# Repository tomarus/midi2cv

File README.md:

MIARPH * MIDI2CV + ARPEGGIATOR
==============================

Miarph is an Arduino based MIDI2CV converter with 4 0-5V 12 bit DAC's and 10 trigger outputs.

## Features

* 4 individual 0-5v 12 bit DAC's (MCP4922 based)
* 10 Trigger outputs
* Dual Arpeggiator
* SYSEX configurable.
* Two MIDI-CC controller outputs.
* Two Midi Note + Trigger outputs.
* Split note (single channel) or two individual channel operations.
* 8 individually programmable gate triggers to be either drum trigger or clock divider.

## Building Notes

* Use a real Arduino Nano or atleast one with a real FTDI chip.
* There is no tuning possibility, but a stable LM7805 is key.
* The LED is on the wrong side but easy fixable using 2 short wires. (This is the only mistake on the PCB).
* The LED resistor is dependent on your LED specs.
* Capacitors have three holes, always use the square one and one of the others. Both 2.54mm and 5.08mm caps will fit.
* Polarized caps should have their positive in the square hole and the negative pointing outwards the board. (See image above!)
* Remove the jumper and power cable before programming!
* DO NOT CONNECT POWER AND USB AT THE SAME TIME!

## BUGS

* It crashes at split note change. But after a reset it is correctly read from eeprom.
* Transpose is buggy, but required because it can only support 60 MIDI notes.

## Programming Using Webconfig

See https://midi.tomarus.io/miarph/

You need a modern browser like Opera or Chrome to use this site.

Note that all values are initially *unknown* until you actually change something.
The device has no MIDI output so config values can't be read back.

After initially building the device, you should set all of your defaults once via webconfig.
After changing values it is stored on the device's eeprom and used at the next power up.

## Programming Using the Commandline

Use the ```midi2cv``` Go utility to program the device.

Example:

```./midi2cv write 0x01 0x77```

Where ```0x01``` is the address and ```0x77``` the value.

List of addresses to program:

| Address | Description | Example value |
| -- | -- | -- |
| 0x00 | unused | -- |
| 0x01 | Split keyboard at note | 0x40 (use 0x00 for no split) |
| 0x02 | MIDI 1 Channel | 0x01 |
| 0x03 | MIDI 2 Channel | 0x02 |
| 0x04 | Transpose Channel 1 | 0x40 |
| 0x05 | Transpose Channel 2 | 0x40 |
| 0x06 | Control Change Number Channel 1 | 0x07 (0x07 = volume) |
| 0x07 | Control Change Number Channel 2 | 0x6A (0x6A = filter cutoff) |
| 0x08 | Control Change Channel 1 | 0x01 |
| 0x09 | Control Change Channel 2 | 0x02 |
| 0x0a | Pitchbend Channel 1 | 0x02 (number of notes) |
| 0x0b | Pitchbend Channel 2 | 0x0c (number of notes) |
| 0x0c | Midi Channel 1 sync | 0x00 (00 = use potmeter, otherwise nr of midi clock ticks) |
| 0x0d | Midi Channel 2 sync | 0x00 (00 = use potmeter, otherwise nr of midi clock ticks) |
| 0x0e | Clockticks to advance the clock divider | 0x03 (0x03 = sync to quarter notes) |
| 0x0f | unused | -- |
| 0x10..0x18 | Port Mode (0 = clock divider, 1 = drum trigger) | 0x00 |
| 0x18..0x20 | Port Trigger Note | 0x36 |
| 0x20..0x28 | Port Clock Divider Division (0=1/1, 1=1/2, 2=1/4, 3=1/8, etc) | 0x00 |

## Bill Of Materials

|Designator                   |Package                                 |Quantity|Designation |PartNo|
|-----------------------------|----------------------------------------|--------|------------|------|
|RV1                          |Potentiometer_Alps_RK09K_Single_Vertical|1       |B10K        | |
|NANO                         |Arduino_Nano_Silk                       |1       |Nano v3     | |
|C1                           |GenericCap                              |1       |100uF       | |
|C2                           |GenericCap                              |1       |10uF        | |
|C3,C4,C5,C6,C7,C8,C9         |GenericCap                              |7       |100nF       | |
|D1                           |LED_D3.0mm                              |1       |LED         | |
|D2,D3,D4                     |D_DO-35_SOD27_P7.62mm_Horizontal        |3       |D           | |
|J1                           |PinHeader_1x02_P2.54mm_Vertical         |1       |ProgramJmpr | |
|J2                           |IDC-Header_2x05_P2.54mm_Vertical        |1       |Power       | |
|J3,J14,J15                   |PinSocket_1x04_P2.54mm_Vertical         |3       |Conn_01x04_M| |
|J4,J24,J25                   |PinHeader_1x04_P2.54mm_Vertical         |3       |Conn_01x04_F| |
|J5                           |PinSocket_1x08_P2.54mm_Vertical         |1       |Conn_01x08_M| |
|J6                           |PinHeader_1x08_P2.54mm_Vertical         |1       |Conn_01x08_F| |
|J7                           |Jack_3.5mm_QingPu_WQP-PJ366ST_Vertical  |1       |Midi Input  | |
|J8-J13,J16-J23               |Jack_3.5mm_QingPu_WQP-PJ398SM_Vertical  |14      |Misc        | |
|R1,R2                        |R_Axial_DIN0207_L6.3mm_D2.5mm_P7.62mm   |2       |2K2         | |
|R3,R4,R5,R6                  |R_Axial_DIN0207_L6.3mm_D2.5mm_P7.62mm   |4       |1K          | |
|R7                           |R_Axial_DIN0207_L6.3mm_D2.5mm_P7.62mm   |1       |220         | |
|R8,R9,R10,R11,R12,R13,R14,R15|R_Axial_DIN0207_L6.3mm_D2.5mm_P7.62mm   |8       |100         | |
|U1                           |TO-220-3_Horizontal_TabDown             |1       |L7805       | |
|U2                           |DIP-8_W7.62mm                           |1       |24LC256     | |
|U5                           |DIP-4_W7.62mm                           |1       |PC817       | PC817XNNSZ1B |
|U6,U8                        |DIP-14_W7.62mm                          |2       |TL074       | |
|U7                           |DIP-16_W7.62mm                          |1       |74HC595     | |
|U3,U4                        |DIP-14_W7.62mm                          |2       |MCP4922     | |

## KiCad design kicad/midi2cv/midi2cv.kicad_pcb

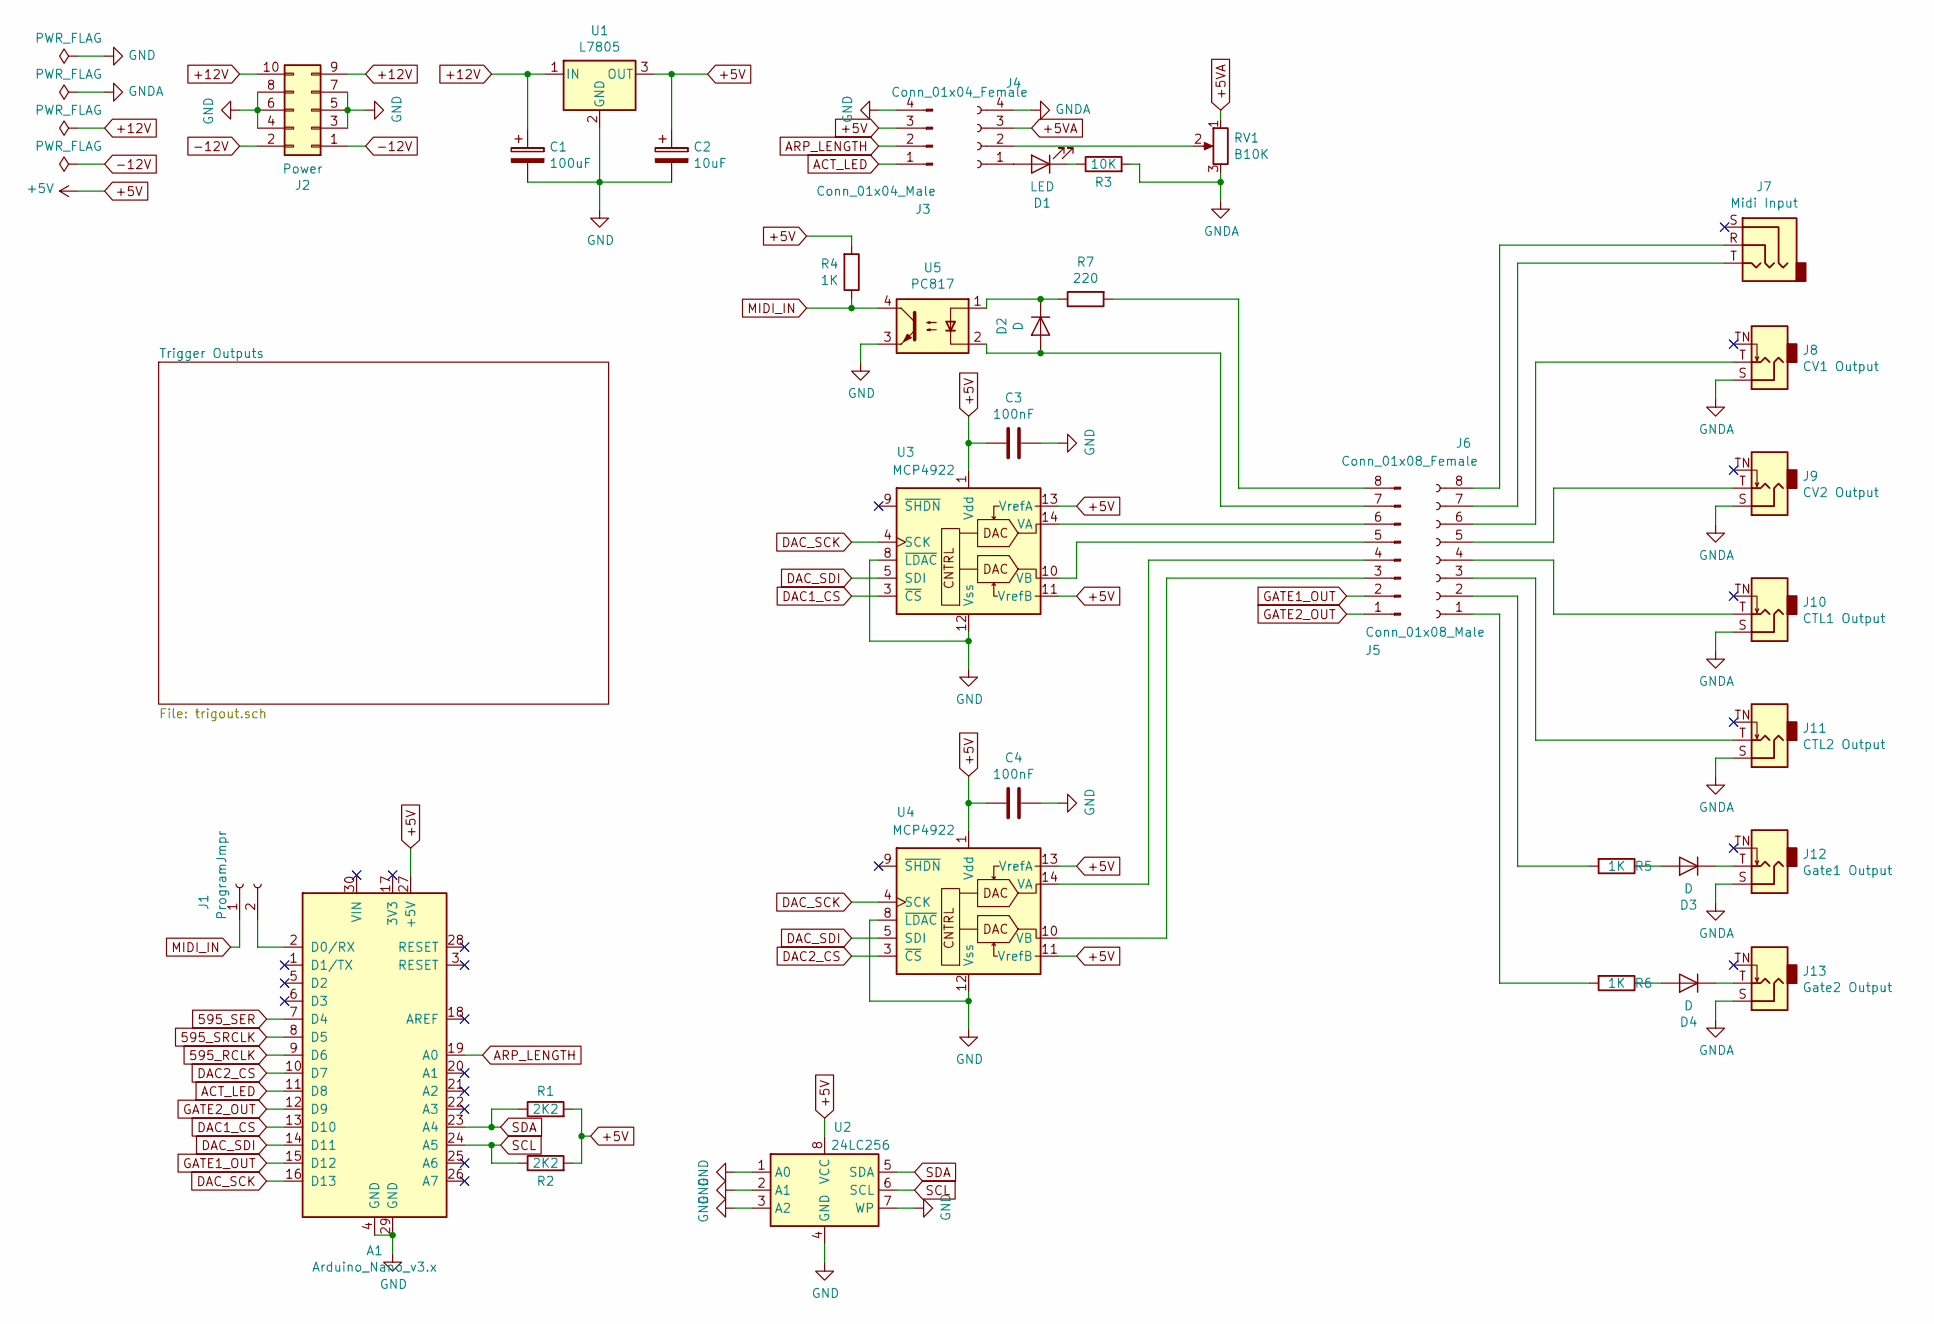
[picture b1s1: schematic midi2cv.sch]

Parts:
A1: Arduino_Nano_v3.x; Arduino_Nano_Silk
C1: 100uF; GenericCap
C2: 10uF; GenericCap
C3, C4: 100nF; GenericCap
D1: LED; LED_D3.0mm
D2, D3, D4: D; D_DO-35_SOD27_P7.62mm_Horizontal
J1: ProgramJmpr; PinHeader_1x02_P2.54mm_Vertical
J2: Power; IDC-Header_2x05_P2.54mm_Vertical
J3: Conn_01x04_Male; PinSocket_1x04_P2.54mm_Vertical
J4: Conn_01x04_Female; PinHeader_1x04_P2.54mm_Vertical
J5: Conn_01x08_Male; PinSocket_1x08_P2.54mm_Vertical
J6: Conn_01x08_Female; PinHeader_1x08_P2.54mm_Vertical
J7: Midi Input; Jack_3.5mm_QingPu_WQP-PJ366ST_Vertical_CircularHoles
J8: CV1 Output; Jack_3.5mm_QingPu_WQP-PJ398SM_Vertical_CircularHoles
J9: CV2 Output; Jack_3.5mm_QingPu_WQP-PJ398SM_Vertical_CircularHoles
J10: CTL1 Output; Jack_3.5mm_QingPu_WQP-PJ398SM_Vertical_CircularHoles
J11: CTL2 Output; Jack_3.5mm_QingPu_WQP-PJ398SM_Vertical_CircularHoles
J12: Gate1 Output; Jack_3.5mm_QingPu_WQP-PJ398SM_Vertical_CircularHoles
J13: Gate2 Output; Jack_3.5mm_QingPu_WQP-PJ398SM_Vertical_CircularHoles
R1, R2: 2K2; R_Axial_DIN0207_L6.3mm_D2.5mm_P7.62mm_Horizontal
R3: 10K; R_Axial_DIN0207_L6.3mm_D2.5mm_P7.62mm_Horizontal
R4, R5, R6: 1K; R_Axial_DIN0207_L6.3mm_D2.5mm_P7.62mm_Horizontal
R7: 220; R_Axial_DIN0207_L6.3mm_D2.5mm_P7.62mm_Horizontal
RV1: B10K; Potentiometer_Alps_RK09K_Single_Vertical
U1: L7805; TO-220-3_Horizontal_TabDown
U2: 24LC256; DIP-8_W7.62mm
U3, U4: MCP4922; DIP-14_W7.62mm
U5: PC817; DIP-4_W7.62mm

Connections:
595_RCLK: A1.9 (D6); also elsewhere on the board
595_SER: A1.7 (D4); also elsewhere on the board
595_SRCLK: A1.8 (D5); also elsewhere on the board
+5V: A1.27 (+5V), C2.1, C3.1, C4.1, J3.3, R1.2, R2.2, R4.2, U1.3 (OUT), U2.8 (VCC), U3.1 (Vdd), U3.11 (VrefB), U3.13 (VrefA), U4.1 (Vdd), U4.11 (VrefB), U4.13 (VrefA); also elsewhere on the board
+5VA: J4.3, RV1.1
+12V: C1.1, J2.9, J2.10, U1.1 (IN); also elsewhere on the board
-12V: J2.1, J2.2; also elsewhere on the board
ACT_LED: A1.11 (D8), J3.1
ARP_LENGTH: A1.19 (A0), J3.2
DAC1_CS: A1.13 (D10), U3.3 (~CS)
DAC2_CS: A1.10 (D7), U4.3 (~CS)
DAC_SCK: A1.16 (D13), U3.4 (SCK), U4.4 (SCK)
DAC_SDI: A1.14 (D11), U3.5 (SDI), U4.5 (SDI)
GATE1_OUT: A1.15 (D12), J5.2
GATE2_OUT: A1.12 (D9), J5.1
GND: A1.4 (GND), A1.29 (GND), C1.2, C2.2, C3.2, C4.2, J2.3, J2.4, J2.5, J2.6, J2.7, J2.8, J3.4, U1.2 (GND), U2.1 (A0), U2.2 (A1), U2.3 (A2), U2.4 (GND), U2.7 (WP), U3.8 (~LDAC), U3.12 (Vss), U4.8 (~LDAC), U4.12 (Vss), U5.3; also elsewhere on the board
GNDA: J4.4, J8.S, J9.S, J10.S, J11.S, J12.S, J13.S, R3.2, RV1.3; also elsewhere on the board
MIDI_IN: J1.1, R4.1, U5.4
unnamed: A1.2 (D0/RX), J1.2
unnamed: D1.1 (K), R3.1
unnamed: D1.2 (A), J4.1
unnamed: D2.1 (K), R7.1, U5.1
unnamed: D2.2 (A), J5.7, U5.2
unnamed: D3.1 (K), J12.T
unnamed: D3.2 (A), R5.1
unnamed: D4.1 (K), J13.T
unnamed: D4.2 (A), R6.1
unnamed: J4.2, RV1.2
unnamed: J5.3, U4.10 (VB)
unnamed: J5.4, U4.14 (VA)
unnamed: J5.5, U3.10 (VB)
unnamed: J5.6, U3.14 (VA)
unnamed: J5.8, R7.2
unnamed: J6.1, R6.2
unnamed: J6.2, R5.2
unnamed: J6.5, J9.T
unnamed: J6.6, J8.T
unnamed: J6.7, J7.T
unnamed: J6.8, J7.R
unnamed: J6.4, J10.T
unnamed: J6.3, J11.T
SCL: A1.24 (A5), R2.1, U2.6 (SCL)
SDA: A1.23 (A4), R1.1, U2.5 (SDA)

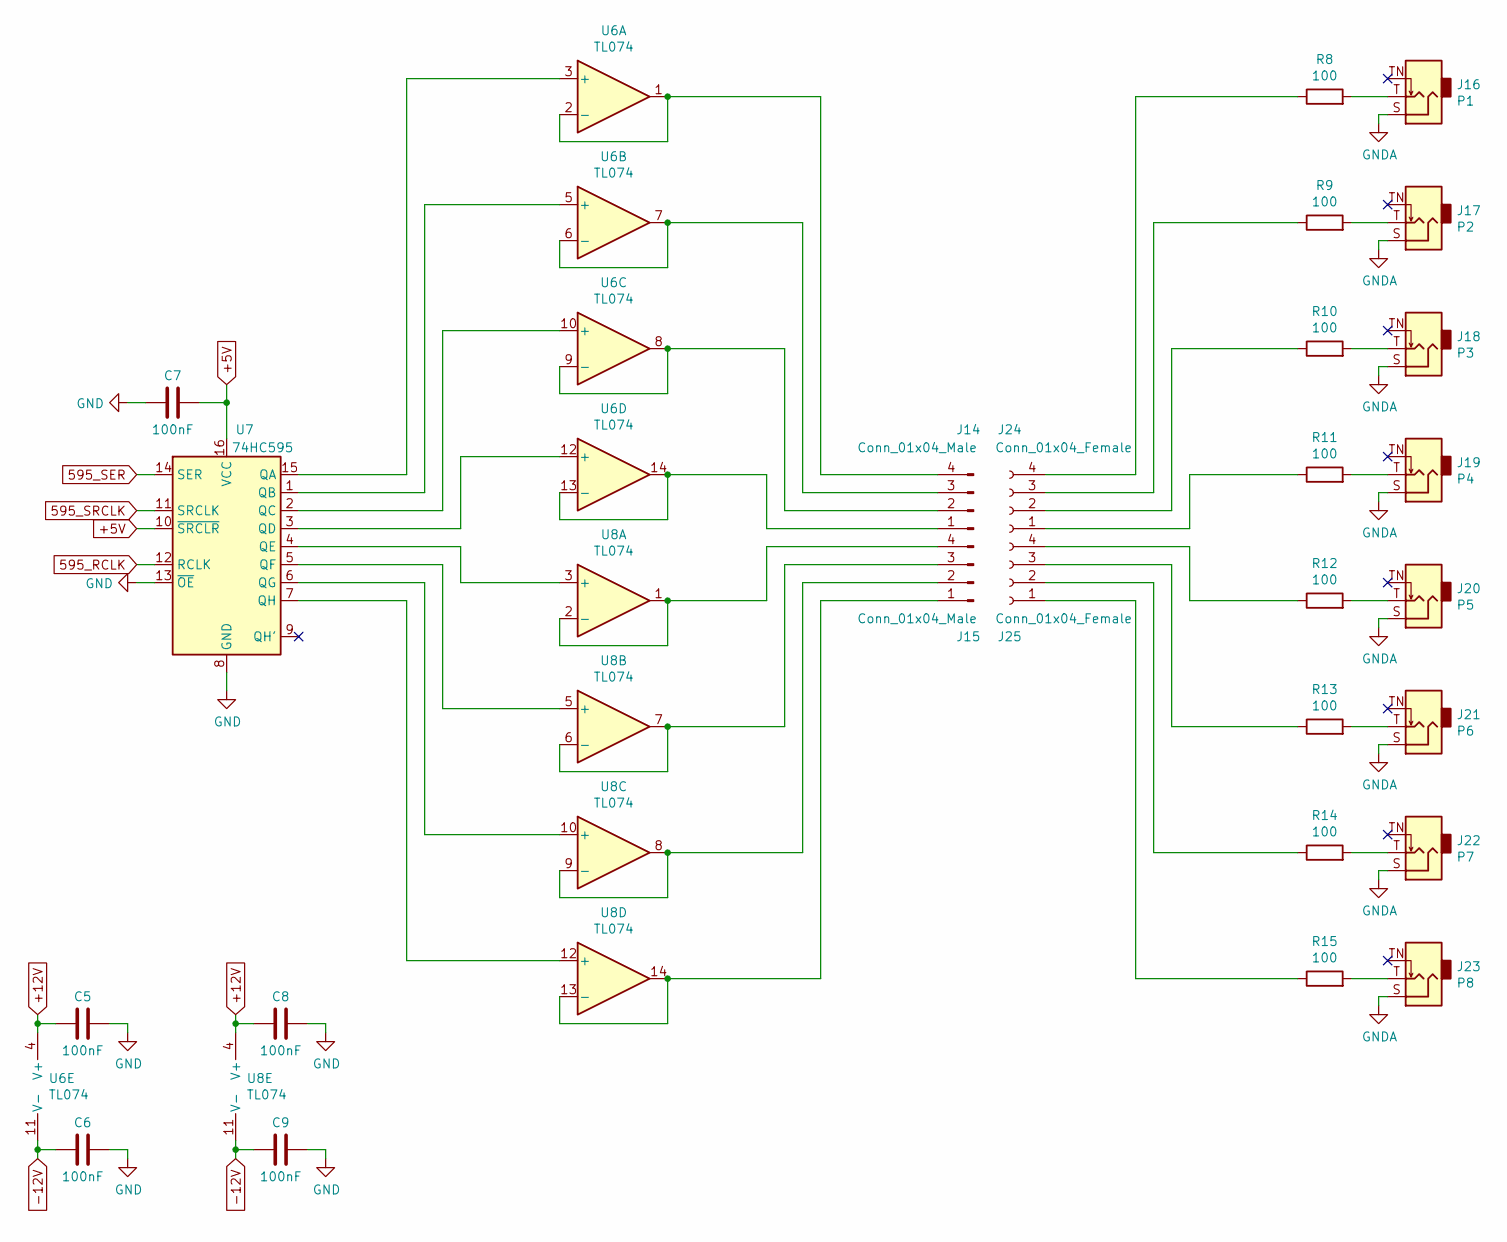
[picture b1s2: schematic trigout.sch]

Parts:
C5, C6, C7, C8, C9: 100nF; GenericCap
J14, J15: Conn_01x04_Male; PinSocket_1x04_P2.54mm_Vertical
J16: P1; Jack_3.5mm_QingPu_WQP-PJ398SM_Vertical_CircularHoles
J17: P2; Jack_3.5mm_QingPu_WQP-PJ398SM_Vertical_CircularHoles
J18: P3; Jack_3.5mm_QingPu_WQP-PJ398SM_Vertical_CircularHoles
J19: P4; Jack_3.5mm_QingPu_WQP-PJ398SM_Vertical_CircularHoles
J20: P5; Jack_3.5mm_QingPu_WQP-PJ398SM_Vertical_CircularHoles
J21: P6; Jack_3.5mm_QingPu_WQP-PJ398SM_Vertical_CircularHoles
J22: P7; Jack_3.5mm_QingPu_WQP-PJ398SM_Vertical_CircularHoles
J23: P8; Jack_3.5mm_QingPu_WQP-PJ398SM_Vertical_CircularHoles
J24, J25: Conn_01x04_Female; PinHeader_1x04_P2.54mm_Vertical
R8, R9, R10, R11, R12, R13, R14, R15: 100; R_Axial_DIN0207_L6.3mm_D2.5mm_P7.62mm_Horizontal
U6, U8: TL074; DIP-14_W7.62mm
U7: 74HC595; DIP-16_W7.62mm

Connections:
595_RCLK: U7.12 (RCLK); also elsewhere on the board
595_SER: U7.14 (SER); also elsewhere on the board
595_SRCLK: U7.11 (SRCLK); also elsewhere on the board
+5V: C7.1, U7.10 (~SRCLR), U7.16 (VCC); also elsewhere on the board
+12V: C5.2, C8.2, U6.4 (V+), U8.4 (V+); also elsewhere on the board
-12V: C6.2, C9.2, U6.11 (V-), U8.11 (V-); also elsewhere on the board
GND: C5.1, C6.1, C7.2, C8.1, C9.1, U7.8 (GND), U7.13 (~OE); also elsewhere on the board
GNDA: J16.S, J17.S, J18.S, J19.S, J20.S, J21.S, J22.S, J23.S; also elsewhere on the board
unnamed: J14.1, U6.13 (-), U6.14
unnamed: J14.2, U6.8, U6.9 (-)
unnamed: J14.3, U6.6 (-), U6.7
unnamed: J14.4, U6.1, U6.2 (-)
unnamed: J15.1, U8.13 (-), U8.14
unnamed: J15.2, U8.8, U8.9 (-)
unnamed: J15.3, U8.6 (-), U8.7
unnamed: J15.4, U8.1, U8.2 (-)
unnamed: J16.T, R8.2
unnamed: J17.T, R9.2
unnamed: J18.T, R10.2
unnamed: J19.T, R11.2
unnamed: J20.T, R12.2
unnamed: J21.T, R13.2
unnamed: J22.T, R14.2
unnamed: J23.T, R15.2
unnamed: J24.1, R11.1
unnamed: J24.2, R10.1
unnamed: J24.3, R9.1
unnamed: J24.4, R8.1
unnamed: J25.1, R15.1
unnamed: J25.2, R14.1
unnamed: J25.3, R13.1
unnamed: J25.4, R12.1
unnamed: U6.3 (+), U7.15 (QA)
unnamed: U6.5 (+), U7.1 (QB)
unnamed: U6.10 (+), U7.2 (QC)
unnamed: U6.12 (+), U7.3 (QD)
unnamed: U7.4 (QE), U8.3 (+)
unnamed: U7.5 (QF), U8.5 (+)
unnamed: U7.6 (QG), U8.10 (+)
unnamed: U7.7 (QH), U8.12 (+)

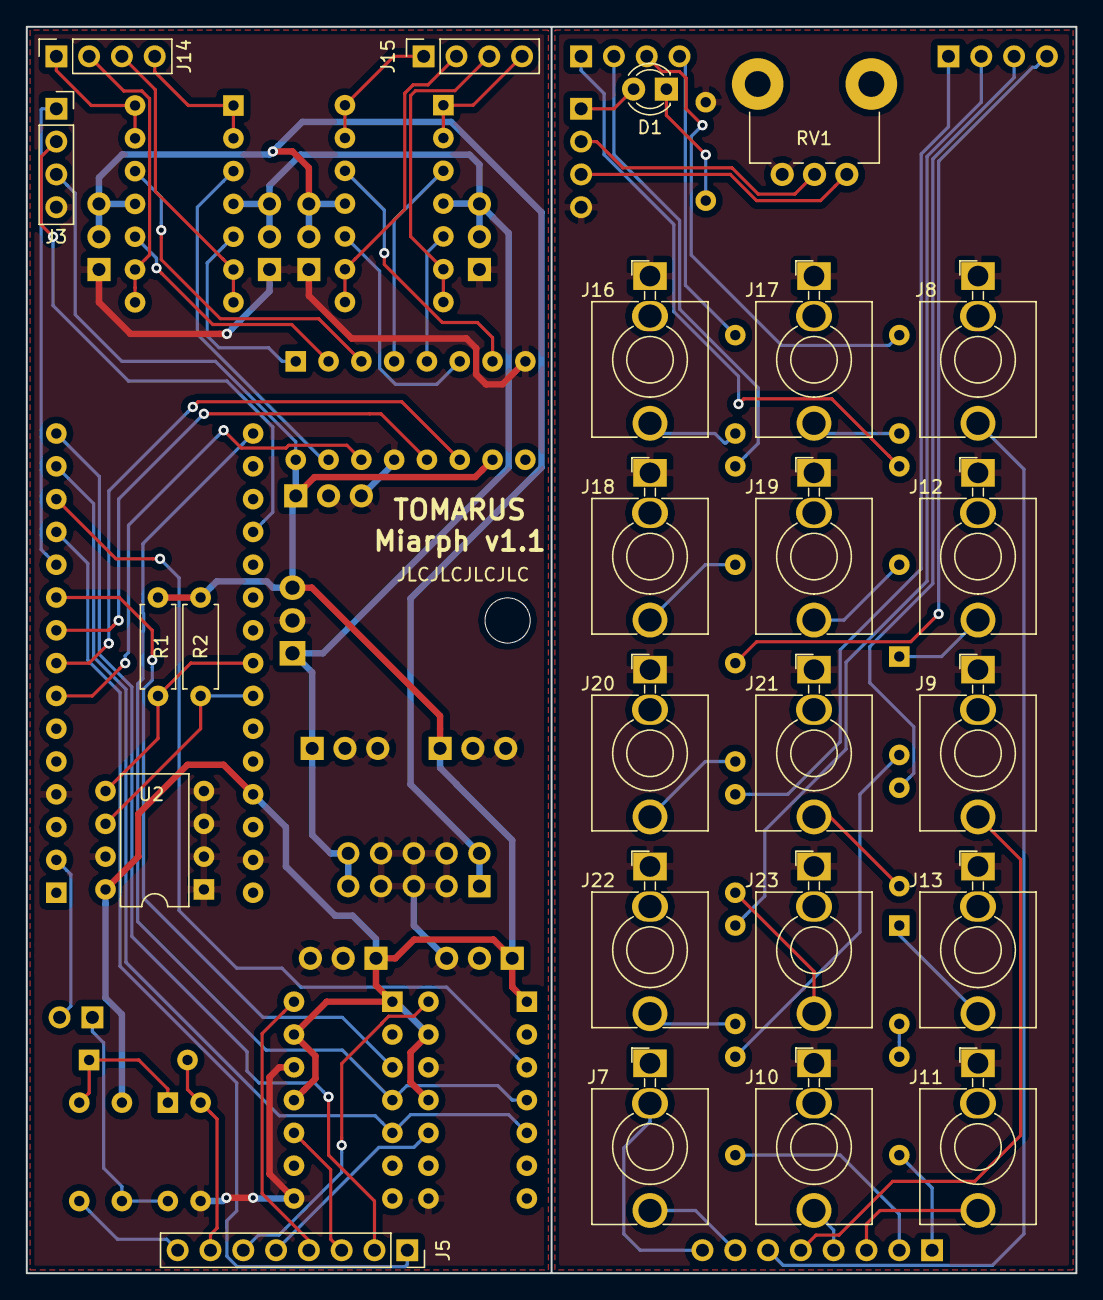
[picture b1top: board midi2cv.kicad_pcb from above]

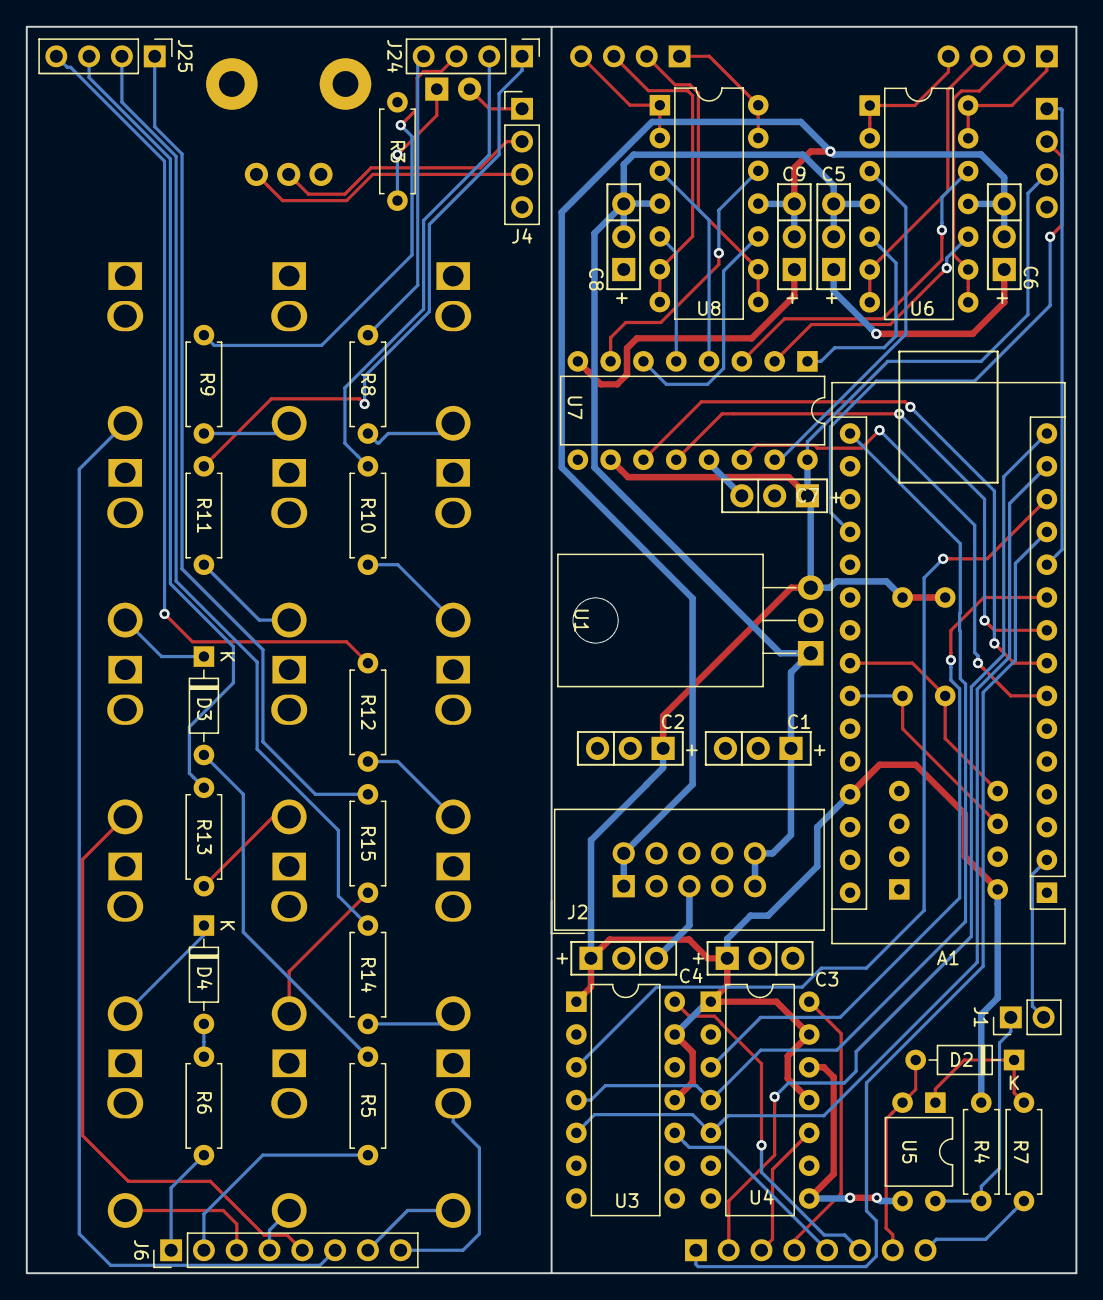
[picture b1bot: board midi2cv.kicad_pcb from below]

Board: 2 copper layers, 81.3 x 96.5 mm, 63 parts (39 on the bottom side), 75 nets.

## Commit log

2019-05-20 Initial commit.
2019-05-23 Create pcb.
2019-05-23 Add frontpanel.
2019-05-23 Add frontpanel kicad project.
2019-05-23 Update frontpanel.
2019-05-23 Add .gitignore.
2019-05-23 Remove bak files.
2019-05-24 Update some symbols + footprints.
2019-05-24 Small production updates.
2019-05-24 Fix a gnd connection.
2019-05-24 Production 1.0
2019-06-08 More test code.
2019-06-08 Add README + image.
2019-06-09 Update code a bit, use config, fix some bugs.
2019-06-10 Fix some bugs and remove some old code.
2019-06-15 Handle pitchbend.
2019-06-15 Add more images/videos.
2019-06-16 Add better configurable clock divider, add arp speed via midi + config test.
2019-06-22 Add dual channel arpeggiator and keyboard split mode.
2019-06-22 Add a table of programmable addresses.
2019-06-23 Small formatting updates.
2019-06-26 Fix caps silkscreen + powerconnector.
2019-07-07 Start on webconfig.
2019-07-07 Update docs for webconfig.
2019-07-07 Add some build notes.
2019-07-07 Remove unused code.
2019-07-07 Documentation updates
2019-07-07 Enlarge transpose range.
2019-07-07 Add more documentation and the BOM.
2019-07-07 Optimize BOM table a bit.
2019-07-07 Update screenshot.
2020-02-02 Make trigger ports configurable as either drum trigger or clock divider.
